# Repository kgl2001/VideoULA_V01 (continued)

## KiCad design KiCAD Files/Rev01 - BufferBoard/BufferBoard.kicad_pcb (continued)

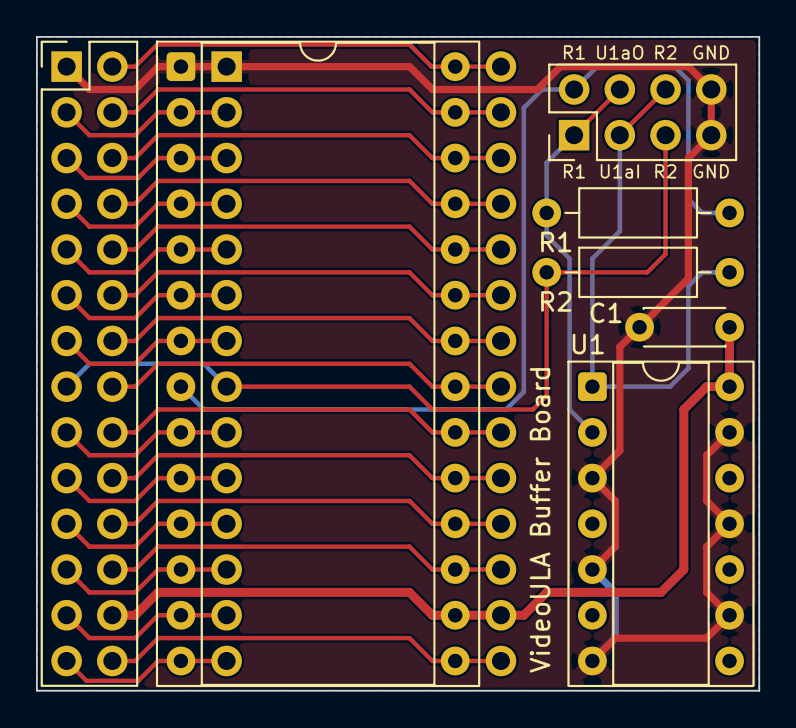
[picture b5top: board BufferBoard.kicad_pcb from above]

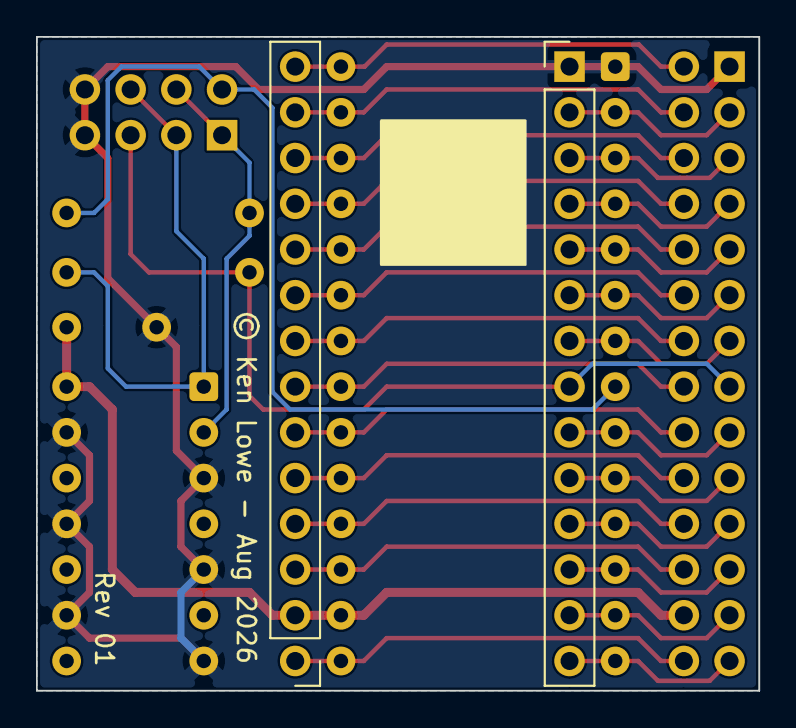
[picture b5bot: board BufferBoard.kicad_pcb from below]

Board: 2 copper layers, 40.1 x 36.3 mm, 9 parts (2 on the bottom side), 31 nets.

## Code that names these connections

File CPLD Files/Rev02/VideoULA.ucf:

# VideoULA V01 Rev02 - pin assignments (XC9572XL-VQ44)
# Derived from the KiCad schematic for hardware Rev02.
# CLK_6M: drives the SAA5050 in the 48MHz build only (high-Z in the 16MHz build).
NET "A"  LOC = "P42"  ;
NET "B"  LOC = "P12"  ;
NET "B_IN"  LOC = "P8"  ;
NET "CLK_1M"  LOC = "P40"  ;
NET "CLK_2M"  LOC = "P1"  ;
NET "CLK_4M"  LOC = "P2"  ;
NET "CLK_6M"  LOC = "P44"  ;
NET "CLK_8M"  LOC = "P3"  ;
NET "CLK_CRTC"  LOC = "P36"  ;
NET "CLK_IN"  LOC = "P43"  ;
NET "CURSOR"  LOC = "P31"  ;
NET "D<0>"  LOC = "P20"  ;
NET "D<1>"  LOC = "P21"  ;
NET "D<2>"  LOC = "P22"  ;
NET "D<3>"  LOC = "P23"  ;
NET "D<4>"  LOC = "P27"  ;
NET "D<5>"  LOC = "P28"  ;
NET "D<6>"  LOC = "P32"  ;
NET "D<7>"  LOC = "P33"  ;
NET "DISEN"  LOC = "P30"  ;
NET "G"  LOC = "P14"  ;
NET "G_IN"  LOC = "P13"  ;
NET "R"  LOC = "P19"  ;
NET "R_IN"  LOC = "P18"  ;
NET "SRAM_ADDR<0>"  LOC = "P7"  ;
NET "SRAM_ADDR<1>"  LOC = "P6"  ;
NET "SRAM_ADDR<2>"  LOC = "P5"  ;
NET "SRAM_ADDR<3>"  LOC = "P16"  ;
NET "SRAM_DATA<0>"  LOC = "P29"  ;
NET "SRAM_DATA<1>"  LOC = "P34"  ;
NET "SRAM_DATA<2>"  LOC = "P37"  ;
NET "SRAM_DATA<3>"  LOC = "P38"  ;
NET "SRAM_nWE"  LOC = "P39"  ;
NET "nCS"  LOC = "P41"  ;
